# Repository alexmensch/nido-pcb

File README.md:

*This respository holds the [Eagle](https://www.autodesk.com/products/eagle/overview) schematic and board CAD files for the Nido smart thermostat sensor printed circuit board (PCB). This PCB connects directly to the Raspberry Pi GPIO header for the simplest possible installation. If you're looking for instructions on how to run Nido on a Raspberry Pi, see https://github.com/alexmensch/nido for instructions and the full project background.*

## Nido PCB v2.0 (Top | CAD | Bottom)

## Bill of Materials (BOM)

Item | Reference | Qty. | Manufacturer  | Part Number   | Package | Type | Notes
:----|:----------|:-----|:--------------|:--------------|:--------|:-----|:-----
1    |JP1        |1     |TE Connectivity|1986712-2		  |         |TH    |Mount on top of board
2    |Q1         |1     |Diodes Inc     |BCW66HTA       |SOT-23-3 |SMD   |
3    |R1-3,R5    |4     |Yageo          |RC0402JR-0710KL|0402     |SMD   |
4    |C2         |1     |Samsung        |CL05A104MP5NNNC|0402     |SMD   |
5    |U2         |1     |IXYS           |CPC1017NTR	    |4-SOP    |SMD   |Align dot on chip with silkscreen dot
6    |U1         |1     |Bosch          |BME280         |8-LGA    |SMD   |Align dot on chip with silkscreen dot
7    |JP2        |1     |Sullins        |PPTC042LFBN-RC |         |TH    |Mount on bottom of board

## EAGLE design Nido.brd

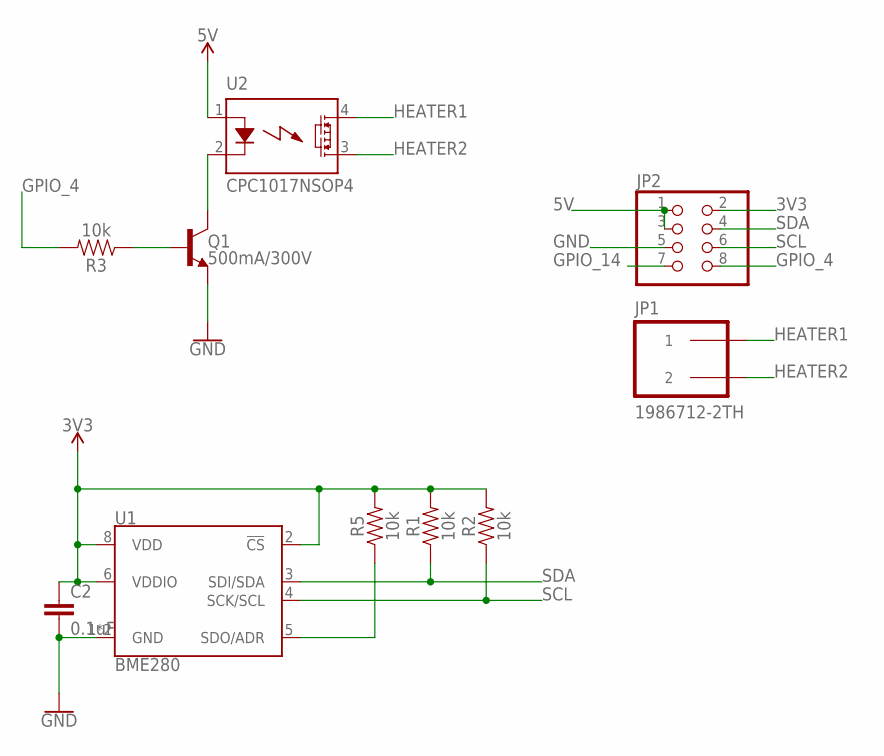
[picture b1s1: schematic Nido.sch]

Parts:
C2: 0.1uF; 0402
JP1: 1986712-2TH; 1986712-2
JP2: PINHD-2X4; 2X04
Q1: 500mA/300V; SOT23-3
R1, R2, R3, R5: 10k; 0402
U1: BME280; LGA-8-2.5X2.5
U2: CPC1017NSOP4; CPC1017N

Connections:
3V3: C2.1, JP2.2, R1.2, R2.2, R5.2, U1.2 (!CS), U1.6 (VDDIO), U1.8 (VDD)
5V: JP2.1, JP2.3, U2.1 (+CONTROL)
GND: C2.2, JP2.5, Q1.2 (E), U1.1 (GND), U1.7 (GND)
GPIO_4: JP2.8, R3.2
GPIO_14: JP2.7
HEATER1: JP1.P$1 (1), JP1.P$2 (1), U2.4 (LOAD2)
HEATER2: JP1.P$3 (2), JP1.P$4 (2), U2.3 (LOAD1)
unnamed: R5.1, U1.5 (SDO/ADR)
unnamed: Q1.3 (C), U2.2 (-CONTROL)
unnamed: Q1.1 (B), R3.1
SCL: JP2.6, R2.1, U1.4 (SCK/SCL)
SDA: JP2.4, R1.1, U1.3 (SDI/SDA)

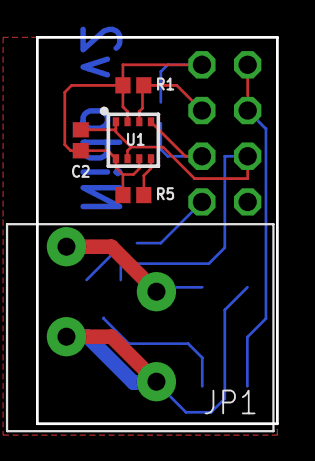
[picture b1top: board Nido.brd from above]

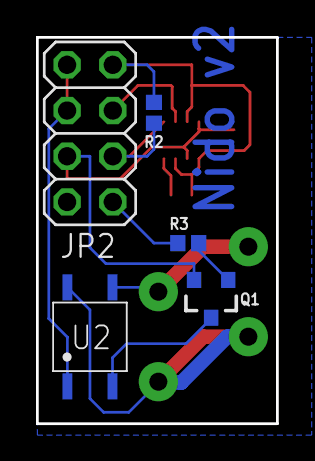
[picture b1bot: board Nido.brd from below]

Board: 2 copper layers, 13.3 x 21.5 mm, 10 parts (5 on the bottom side), 11 nets.

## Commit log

2019-08-05 Initial commit of Eagle board and schematic files
2019-08-06 Updated board components, added PCB photos
2019-08-06 Removed unused nets
2019-12-01 Updated Nido PCB v2 files
2019-12-01 Added Eagle screenshot
2019-12-01 Modifed image dimensions
2019-12-01 Modified image dimensions
2019-12-01 Updated CAD image

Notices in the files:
parts and their libraries:
SparkFun-Resistors: Licensing: Creative Commons ShareAlike 4.0 International - https://creativecommons.org/licenses/by-sa/4.0
